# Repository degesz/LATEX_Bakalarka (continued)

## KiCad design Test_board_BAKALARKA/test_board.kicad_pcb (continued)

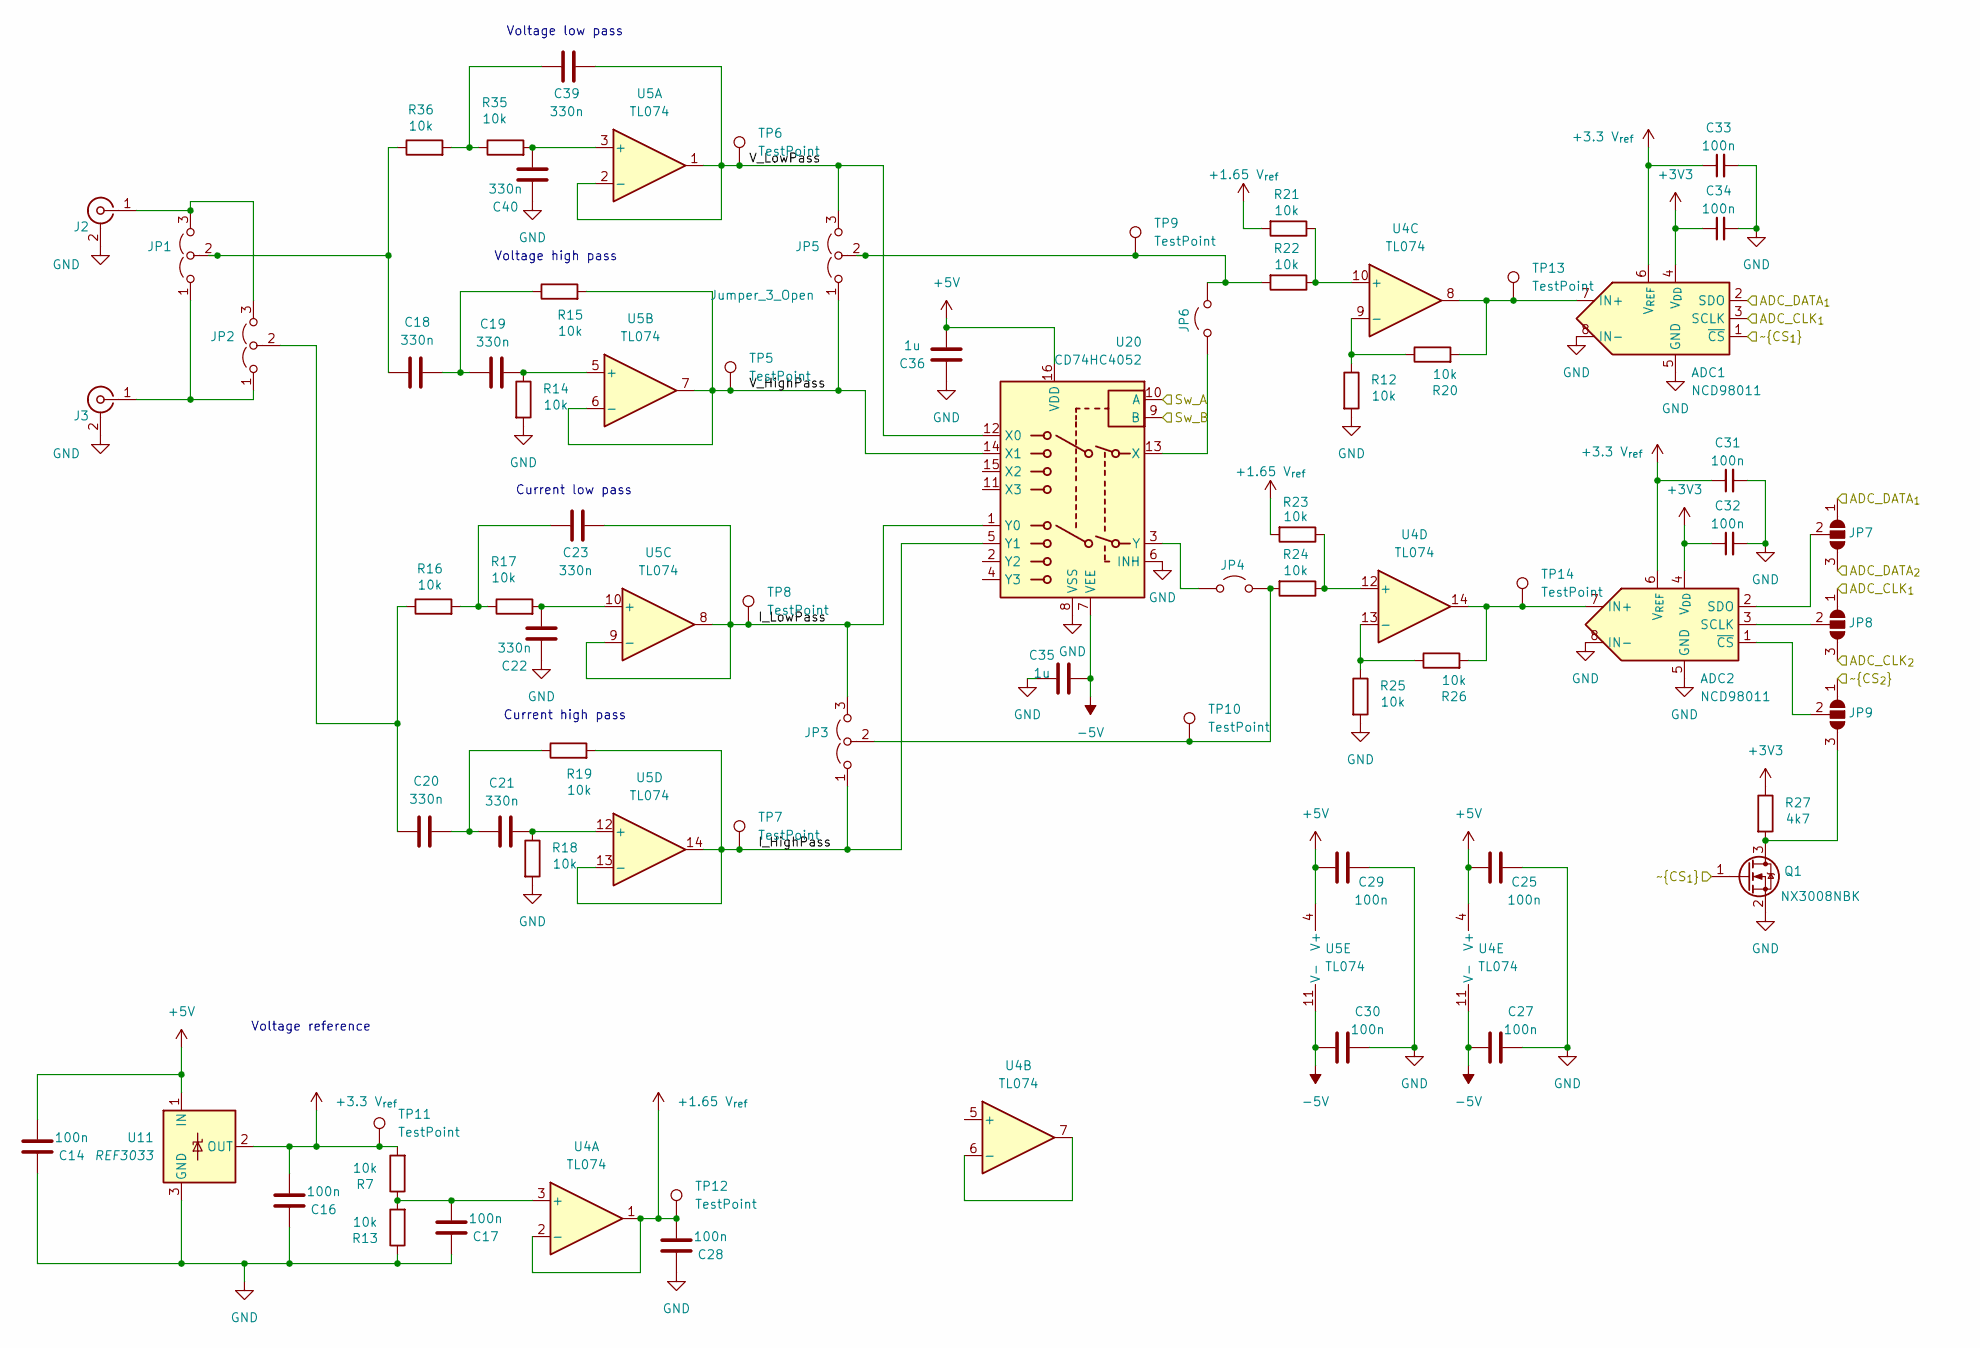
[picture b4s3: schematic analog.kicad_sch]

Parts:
ADC1, ADC2: NCD98011; Texas_UQFN-8_1.5x1.5mm_P0.5mm
C14, C16, C17, C25, C27, C28, C29, C30, C31, C32, C33, C34: 100n; C_0603_1608Metric_Pad1.08x0.95mm_HandSolder
C18, C19, C20, C21, C22, C23, C39, C40: 330n; C_0603_1608Metric_Pad1.08x0.95mm_HandSolder
C35, C36: 1u; C_0603_1608Metric_Pad1.08x0.95mm_HandSolder
J2, J3: Conn_Coaxial; BNC_Amphenol_B6252HB-NPP3G-50_Horizontal
JP1, JP2, JP3, JP5: Jumper_3_Open; PinHeader_1x03_P2.54mm_Vertical
JP4, JP6: Jumper_2_Open; PinHeader_1x02_P2.54mm_Vertical
JP7, JP8, JP9: SolderJumper_3_Open; SolderJumper-3_P1.3mm_Open_RoundedPad1.0x1.5mm
Q1: NX3008NBK; SOT-323_SC-70_Handsoldering
R7, R12, R13, R14, R15, R16, R17, R18, R19, R20, R21, R22, R23, R24, R25, R26, R35, R36: 10k; R_0603_1608Metric_Pad0.98x0.95mm_HandSolder
R27: 4k7; R_0603_1608Metric_Pad0.98x0.95mm_HandSolder
TP5, TP6, TP7, TP8, TP9, TP10, TP11, TP12, TP13, TP14: TestPoint; Pin_D1.0mm_L10.0mm
U4, U5: TL074; TSSOP-14_4.4x5mm_P0.65mm
U11: REF3033; SOT-23
U20: CD74HC4052; TSSOP-16_4.4x5mm_P0.65mm

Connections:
+1.65 V_{ref}: C28.2, R21.2, R23.2, TP12.1, U4.1, U4.2 (-)
+3.3 V_{ref}: ADC1.6 (V_{REF}), ADC2.6 (V_{REF}), C16.2, C31.1, C33.1, R7.2, TP11.1, U11.2 (OUT)
+3V3: ADC1.4 (V_{DD}), ADC2.4 (V_{DD}), C32.1, C34.1, R27.1; also elsewhere on the board
+5V: C14.2, C25.2, C29.2, C36.2, U4.4 (V+), U5.4 (V+), U11.1 (IN), U20.16 (VDD); also elsewhere on the board
-5V: C27.2, C30.2, C35.2, U4.11 (V-), U5.11 (V-), U20.7 (VEE); also elsewhere on the board
/Analog/ADC_CLK_{1}: ADC1.3 (SCLK), JP8.1 (A); also elsewhere on the board
/Analog/ADC_CLK_{2}: JP8.3 (B); also elsewhere on the board
/Analog/ADC_DATA_{1}: ADC1.2 (SDO), JP7.1 (A); also elsewhere on the board
/Analog/ADC_DATA_{2}: JP7.3 (B); also elsewhere on the board
/Analog/I_HighPass: JP3.1 (A), R19.2, TP7.1, U5.13 (-), U5.14, U20.5 (Y1)
/Analog/I_LowPass: C23.1, JP3.3 (B), TP8.1, U5.8, U5.9 (-), U20.1 (Y0)
/Analog/Sw_A: U20.10 (A); also elsewhere on the board
/Analog/Sw_B: U20.9 (B); also elsewhere on the board
/Analog/V_HighPass: JP5.1 (A), R15.2, TP5.1, U5.6 (-), U5.7, U20.14 (X1)
/Analog/V_LowPass: C39.1, JP5.3 (B), TP6.1, U5.1, U5.2 (-), U20.12 (X0)
/Analog/~CS_{1}: ADC1.1 (~CS), Q1.1 (G); also elsewhere on the board
/Analog/~CS_{2}: JP9.1 (A); also elsewhere on the board
GND: ADC1.5 (GND), ADC1.8 (IN-), ADC2.5 (GND), ADC2.8 (IN-), C14.1, C16.1, C17.1, C22.2, C25.1, C27.1, C28.1, C29.1, C30.1, C31.2, C32.2, C33.2, C34.2, C35.1, C36.1, C40.2, J2.2 (Ext), J3.2 (Ext), Q1.2 (S), R12.2, R13.1, R14.2, R18.2, R25.2, U11.3 (GND), U20.6 (INH), U20.8 (VSS); also elsewhere on the board
unnamed: ADC1.7 (IN+), R20.2, TP13.1, U4.8
unnamed: ADC2.7 (IN+), R26.2, TP14.1, U4.14
unnamed: ADC2.3 (SCLK), JP8.2 (C)
unnamed: ADC2.2 (SDO), JP7.2 (C)
unnamed: ADC2.1 (~CS), JP9.2 (C)
unnamed: C18.1, C19.2, R15.1
unnamed: C20.1, C21.2, R19.1
unnamed: C23.2, R16.2, R17.1
unnamed: C39.2, R35.1, R36.2
unnamed: J2.1 (In), JP1.3 (B), JP2.3 (B)
unnamed: J3.1 (In), JP1.1 (A), JP2.1 (A)
unnamed: C18.2, JP1.2 (C), R36.1
unnamed: C20.2, JP2.2 (C), R16.1
unnamed: JP3.2 (C), JP4.2 (B), R24.2, TP10.1
unnamed: JP4.1 (A), U20.3 (Y)
unnamed: JP5.2 (C), JP6.2 (B), R22.2, TP9.1
unnamed: JP6.1 (A), U20.13 (X)
unnamed: JP9.3 (B), Q1.3 (D), R27.2
unnamed: C17.2, R7.1, R13.2, U4.3 (+)
unnamed: U4.6 (-), U4.7
unnamed: R21.1, R22.1, U4.10 (+)
unnamed: R12.1, R20.1, U4.9 (-)
unnamed: R23.1, R24.1, U4.12 (+)
unnamed: R25.1, R26.1, U4.13 (-)
unnamed: C40.1, R35.2, U5.3 (+)
unnamed: C19.1, R14.1, U5.5 (+)
unnamed: C22.1, R17.2, U5.10 (+)
unnamed: C21.1, R18.1, U5.12 (+)

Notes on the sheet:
Current high pass
Current low pass
Voltage low pass
Voltage reference
Voltage high pass

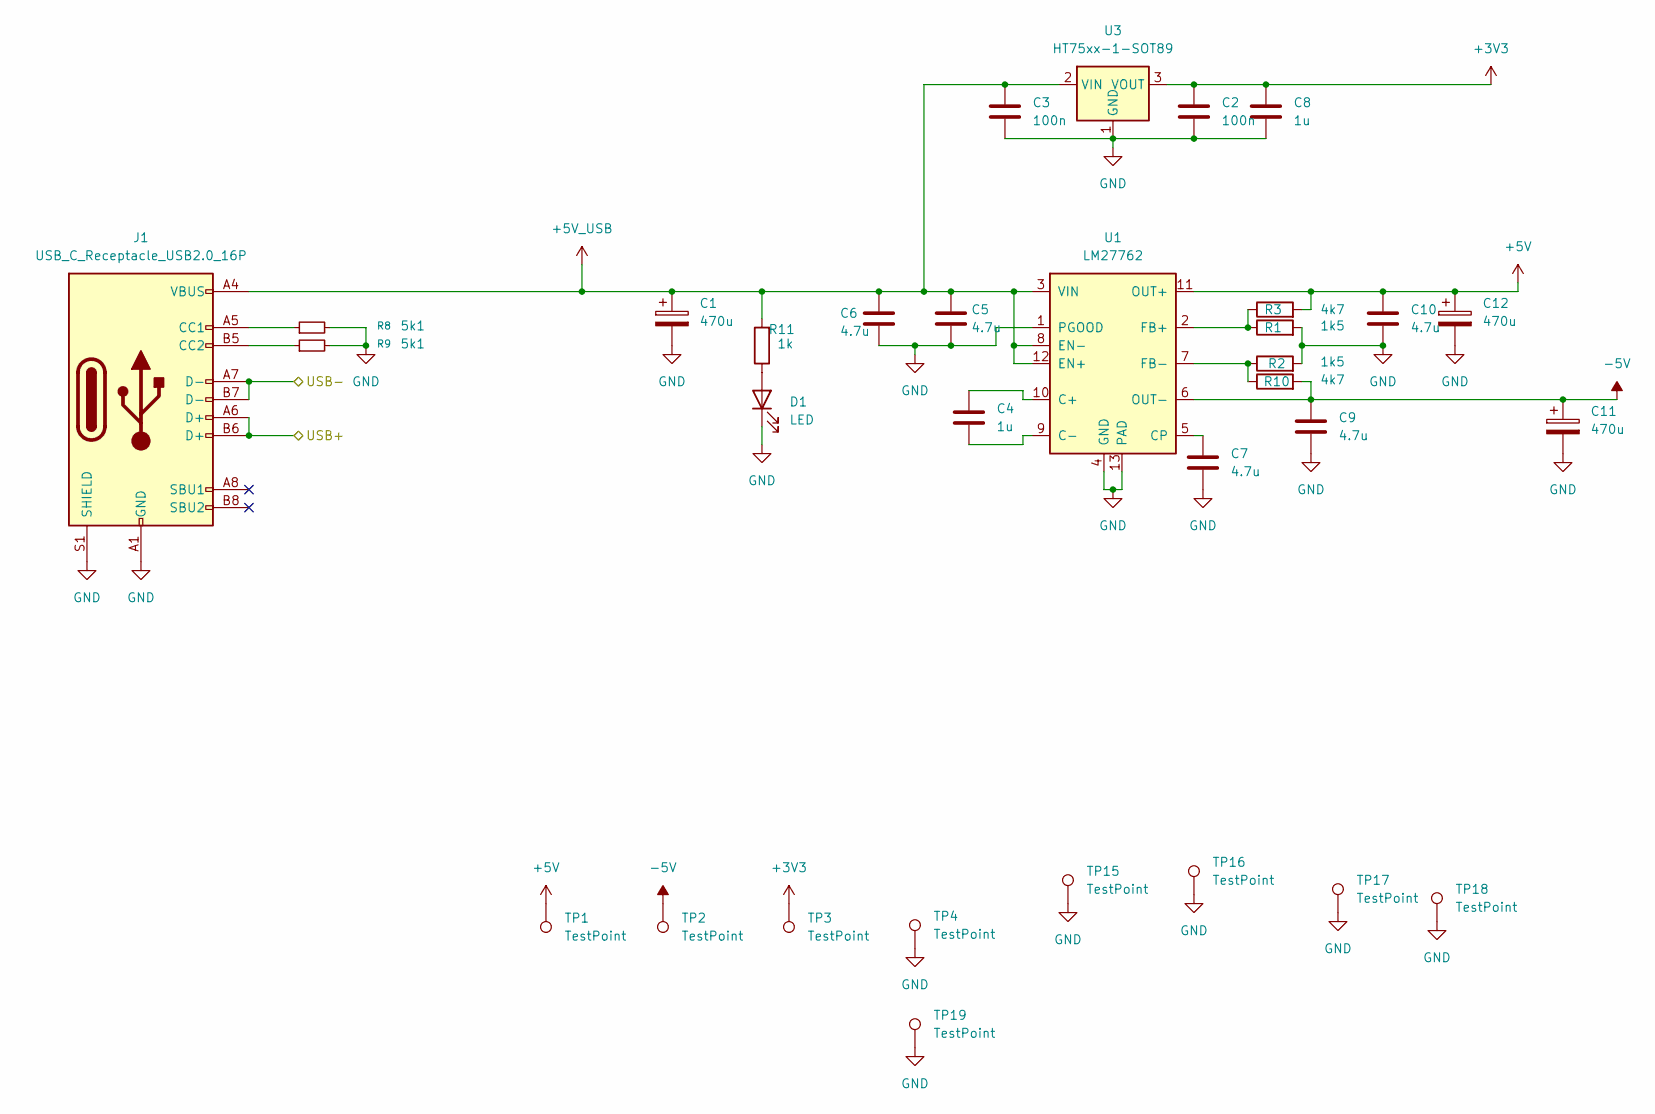
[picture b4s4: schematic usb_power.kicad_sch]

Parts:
C1, C11, C12: 470u; CP_Radial_D8.0mm_P3.80mm
C2, C3: 100n; C_0603_1608Metric_Pad1.08x0.95mm_HandSolder
C4: 1u; R_0603_1608Metric_Pad0.98x0.95mm_HandSolder
C5, C6, C7, C9, C10: 4.7u; C_0805_2012Metric_Pad1.18x1.45mm_HandSolder
C8: 1u; C_0603_1608Metric_Pad1.08x0.95mm_HandSolder
D1: LED; LED_miniPLCC_2315_Handsoldering
J1: USB_C_Receptacle_USB2.0_16P; USB_C_Receptacle_GCT_USB4105-xx-A_16P_TopMnt_Horizontal
R1, R2: 1k5; R_0603_1608Metric_Pad0.98x0.95mm_HandSolder
R3, R10: 4k7; R_0603_1608Metric_Pad0.98x0.95mm_HandSolder
R8, R9: 5k1; R_0603_1608Metric_Pad0.98x0.95mm_HandSolder
R11: 1k; R_0603_1608Metric_Pad0.98x0.95mm_HandSolder
TP1, TP2, TP3, TP4, TP15, TP16, TP17, TP18, TP19: TestPoint; Pin_D1.3mm_L11.0mm_LooseFit
U1: LM27762; WSON-12-1EP_3x2mm_P0.5mm_EP1x2.65_ThermalVias
U3: HT75xx-1-SOT89; SOT-89-3_Handsoldering

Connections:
+3V3: C2.1, C8.1, TP3.1, U3.3 (VOUT); also elsewhere on the board
+5V: C10.1, C12.1, R3.2, TP1.1, U1.11 (OUT+); also elsewhere on the board
+5V_USB: C1.1, C3.1, C5.1, C6.1, J1.A4 (VBUS), J1.A9 (VBUS), J1.B4 (VBUS), J1.B9 (VBUS), R11.2, U1.3 (VIN), U1.8 (EN-), U1.12 (EN+), U3.2 (VIN); also elsewhere on the board
-5V: C9.1, C11.1, R10.2, TP2.1, U1.6 (OUT-); also elsewhere on the board
/USB+Power/USB+: J1.A6 (D+), J1.B6 (D+); also elsewhere on the board
/USB+Power/USB-: J1.A7 (D-), J1.B7 (D-); also elsewhere on the board
GND: C1.2, C2.2, C3.2, C5.2, C6.2, C7.2, C8.2, C9.2, C10.2, C11.2, C12.2, D1.1 (K), J1.A1 (GND), J1.A12 (GND), J1.B1 (GND), J1.B12 (GND), J1.S1 (SHIELD), R1.2, R2.2, R8.2, R9.2, TP4.1, TP15.1, TP16.1, TP17.1, TP18.1, TP19.1, U1.1 (PGOOD), U1.4 (GND), U1.13 (PAD), U3.1 (GND); also elsewhere on the board
unnamed: D1.2 (A), R11.1
unnamed: J1.A5 (CC1), R8.1
unnamed: J1.B5 (CC2), R9.1
unnamed: C4.1, U1.10 (C+)
unnamed: C4.2, U1.9 (C-)
unnamed: C7.1, U1.5 (CP)
unnamed: R1.1, R3.1, U1.2 (FB+)
unnamed: R2.1, R10.1, U1.7 (FB-)

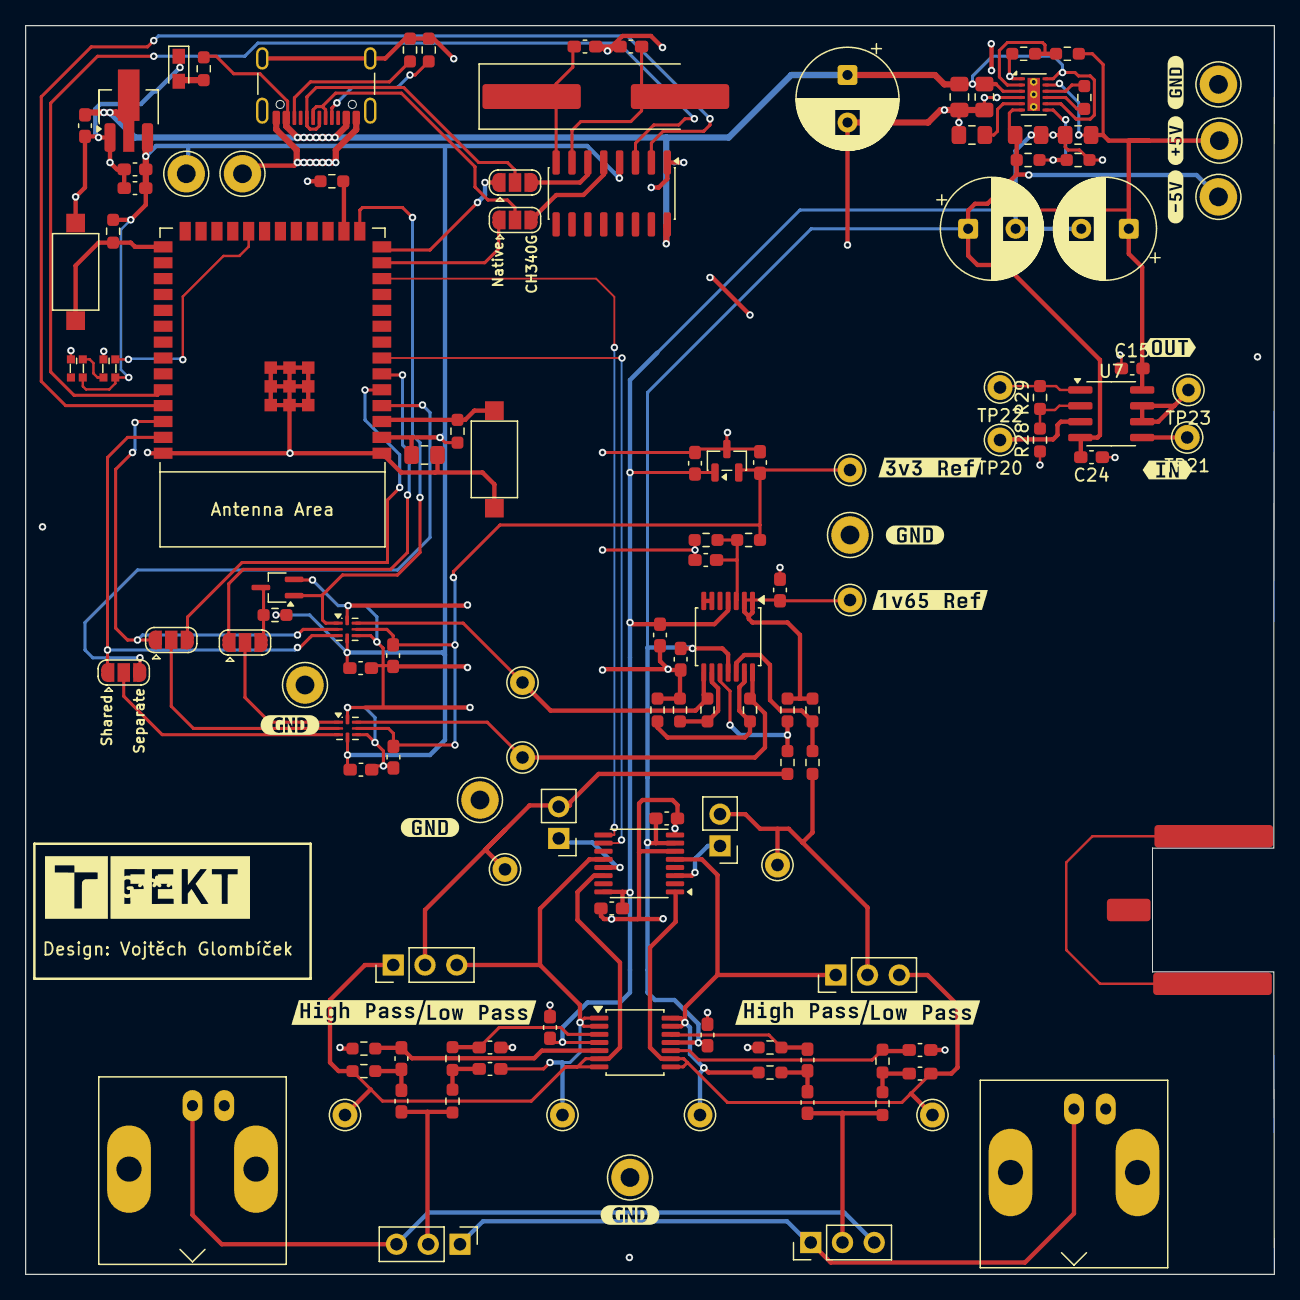
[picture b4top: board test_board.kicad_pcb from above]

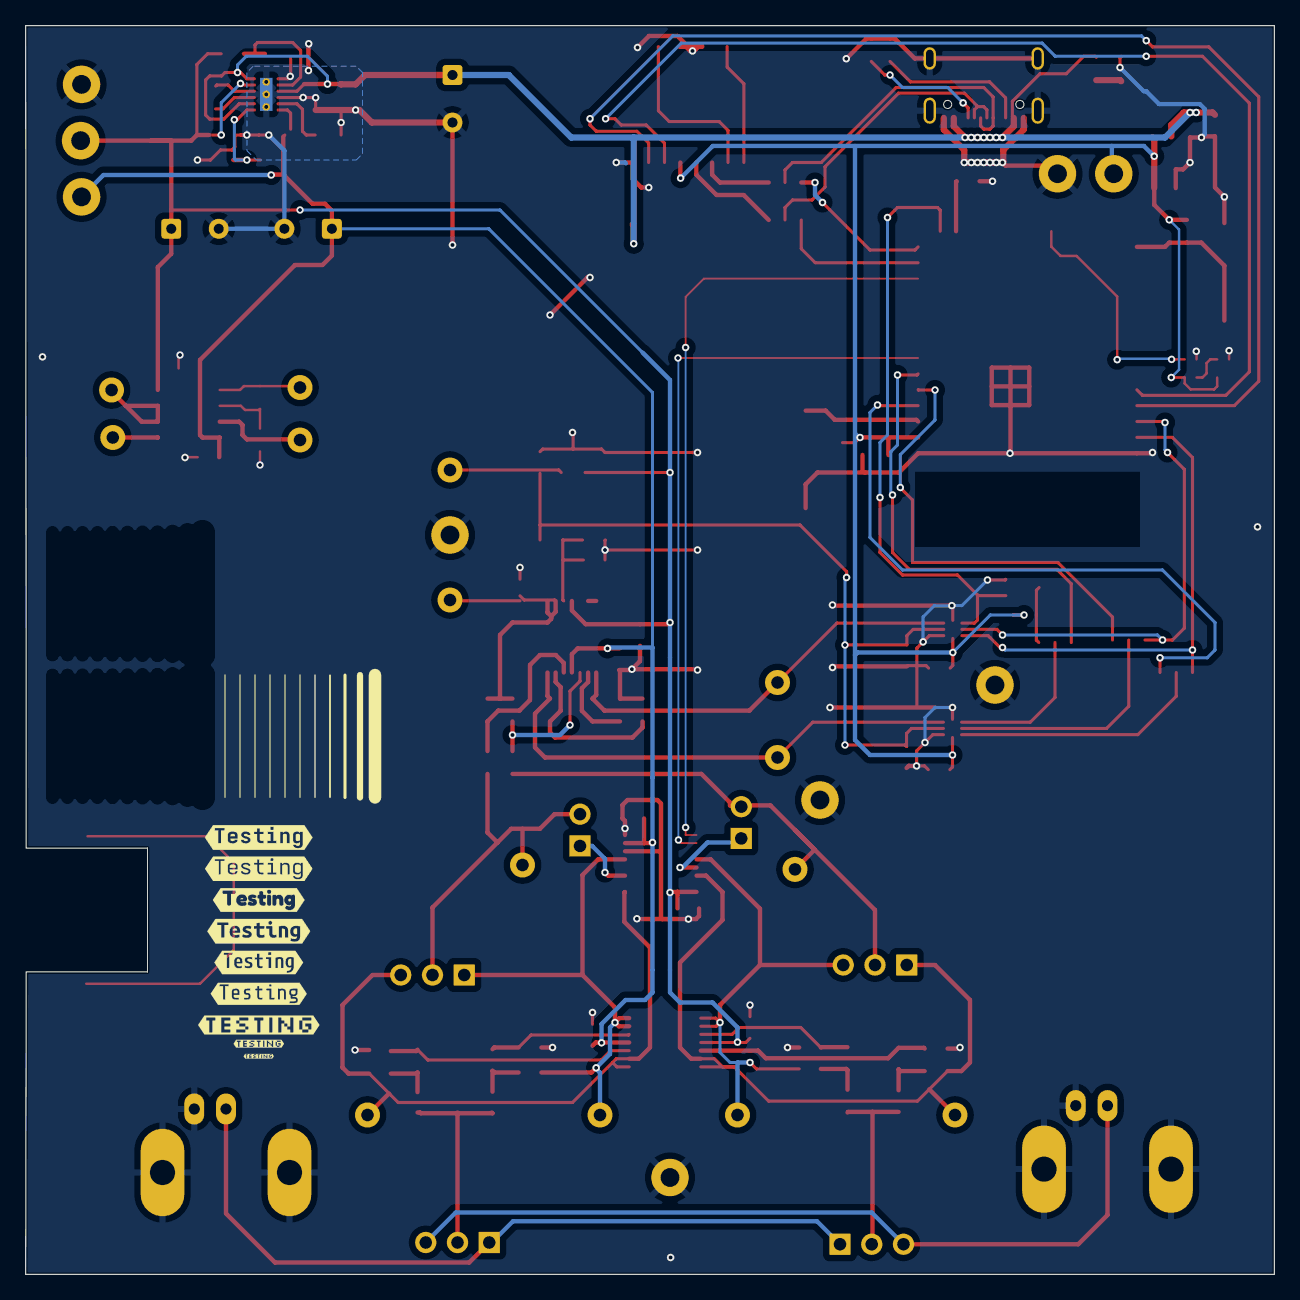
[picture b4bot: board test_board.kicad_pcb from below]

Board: 2 copper layers, 99.9 x 99.9 mm, 150 parts (10 on the bottom side), 75 nets.

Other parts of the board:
kibuzzard-69665B05: G***; kibuzzard-69665B05
kibuzzard-69665B09: G***; kibuzzard-69665B09
kibuzzard-69665B11: G***; kibuzzard-69665B11
kibuzzard-696656D5: G***; kibuzzard-696656D5
kibuzzard-696656FC: G***; kibuzzard-696656FC
kibuzzard-696658C9: G***; kibuzzard-696658C9
kibuzzard-696658E8: G***; kibuzzard-696658E8
kibuzzard-696658F1: G***; kibuzzard-696658F1
kibuzzard-696658F7: G***; kibuzzard-696658F7
kibuzzard-696658FF: G***; kibuzzard-696658FF
kibuzzard-6958001D, kibuzzard-6958001D#2: G***; kibuzzard-6958001D
kibuzzard-6966571E: G***; kibuzzard-6966571E
kibuzzard-6966573E: G***; kibuzzard-6966573E
kibuzzard-6966592B: G***; kibuzzard-6966592B
kibuzzard-6966594C: G***; kibuzzard-6966594C
kibuzzard-69665706: G***; kibuzzard-69665706
kibuzzard-69665710: G***; kibuzzard-69665710
kibuzzard-69665718: G***; kibuzzard-69665718
kibuzzard-69665729: G***; kibuzzard-69665729
kibuzzard-69665736: G***; kibuzzard-69665736
kibuzzard-69665743: G***; kibuzzard-69665743
kibuzzard-69665908: G***; kibuzzard-69665908
kibuzzard-69665967: G***; kibuzzard-69665967

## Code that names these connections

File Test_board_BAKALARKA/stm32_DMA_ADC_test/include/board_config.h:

#pragma once

#include <Arduino.h>

#include <cstdint>

namespace board {

constexpr uint8_t kVoltageHighpassPin = PA1;
constexpr uint8_t kCurrentHighpassPin = PA4;

constexpr uint8_t kOffsetPwmPin = PA7;

constexpr uint8_t kDdsDataPin = PA5;
constexpr uint8_t kDdsFsyncPin = PA6;
constexpr uint8_t kDdsClockPin = PA8;

constexpr uint8_t kShuntRangeLsbPin = PB8;
constexpr uint8_t kShuntRangeMsbPin = PB9;
constexpr uint8_t kCurrentPgaLsbPin = PB10;
constexpr uint8_t kCurrentPgaMsbPin = PB11;
constexpr uint8_t kVoltagePgaLsbPin = PB12;
constexpr uint8_t kVoltagePgaMsbPin = PB13;

constexpr uint8_t kHeartbeatLedPin = PB15;
constexpr bool kHeartbeatActiveHigh = true;

constexpr uint8_t kMcp4561DefaultAddress = 0x2F;

constexpr uint32_t kSerialBaud = 115200;
constexpr uint32_t kDdsMasterClockHz = 16000000UL;

constexpr float kAdcReferenceVolts = 3.3f;
constexpr uint16_t kAdcMaxCode = 4095;
constexpr uint16_t kAdcCenterCode = 2048;

constexpr std::size_t kMaxBurstSamples = 2048;
constexpr uint32_t kDefaultBurstSamples = 500;
constexpr uint32_t kTargetSamplesPerPeriod = 25UL;
constexpr uint32_t kDefaultSampleRateHz = 25000UL;
constexpr uint32_t kMinSampleRateHz = 1000UL;
constexpr uint32_t kMaxSampleRateHz = 1000000UL;

}  // namespace board

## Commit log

2025-11-26 moving one folder up
2025-12-03 prace na test board schem
2025-12-08 pridani textu peak detect, xor phase, signal source
2025-12-09 update rizeni amplitudy
2025-12-21 pridane nastaveni dc offsetu do zdroje a neco ke vzorkovani
2025-12-27 work on lot of things
2025-12-29 prace na prototypu a tak
2026-01-01 pridani zaveru, opraveni chyb, a tak. prepnuti na onepage render
2026-01-05 fix citace a uvod
2026-01-11 obhajoba prezentace
2026-01-17 testboard frontpanel
2026-01-18 front panel and test board ordered
2026-02-22 start work on 2nd 2nd_prototype_LCRmeter
2026-02-24 work on layout proto2
2026-02-26 routing v2 work almost complete
2026-03-05 finished with offset amps
2026-03-10 finished final final_2
2026-03-10 prod
2026-04-02 somewhat working 2nd prototype
2026-04-05 somewhat working, memory issues
2026-04-09 some upgrades to the viewing software. remove calibration
2026-04-14 remake of pc app, improvements
2026-05-01 Removed obsolete PDF files and updated LaTeX documents with new sections and references.
2026-05-01 Update .gitignore to include history files and mark subproject commits as dirty in history files
2026-05-01 gitignor fix
2026-05-06 upgrades to pc app
2026-05-06 gitignore fix
2026-05-06 Stop tracking local schematic history
2026-05-06 export options + cleanup
2026-05-09 neco o appce
2026-05-15 4wire a dalsi
2026-05-19 nejake zpracovani vysledku mereni
2026-05-21 nejake edity vysledku a kompenzace seriovym rezistorem
2026-05-21 slight fixes
2026-05-21 oprava měřicí měřící
2026-05-21 šachy s kapitolama + budoucí vylepšení
2026-05-29 citace + vysledky prelim
2026-05-29 checkpoint before messing with it
2026-05-29 build app
2026-05-29 gitignore change
2026-05-29 prilohy
2026-05-29 prilohy okraje
2026-05-29 format + samovyvazovaci fix
2026-06-01 popisky fix - finish
2026-06-16 Mark bakalarka as complete
